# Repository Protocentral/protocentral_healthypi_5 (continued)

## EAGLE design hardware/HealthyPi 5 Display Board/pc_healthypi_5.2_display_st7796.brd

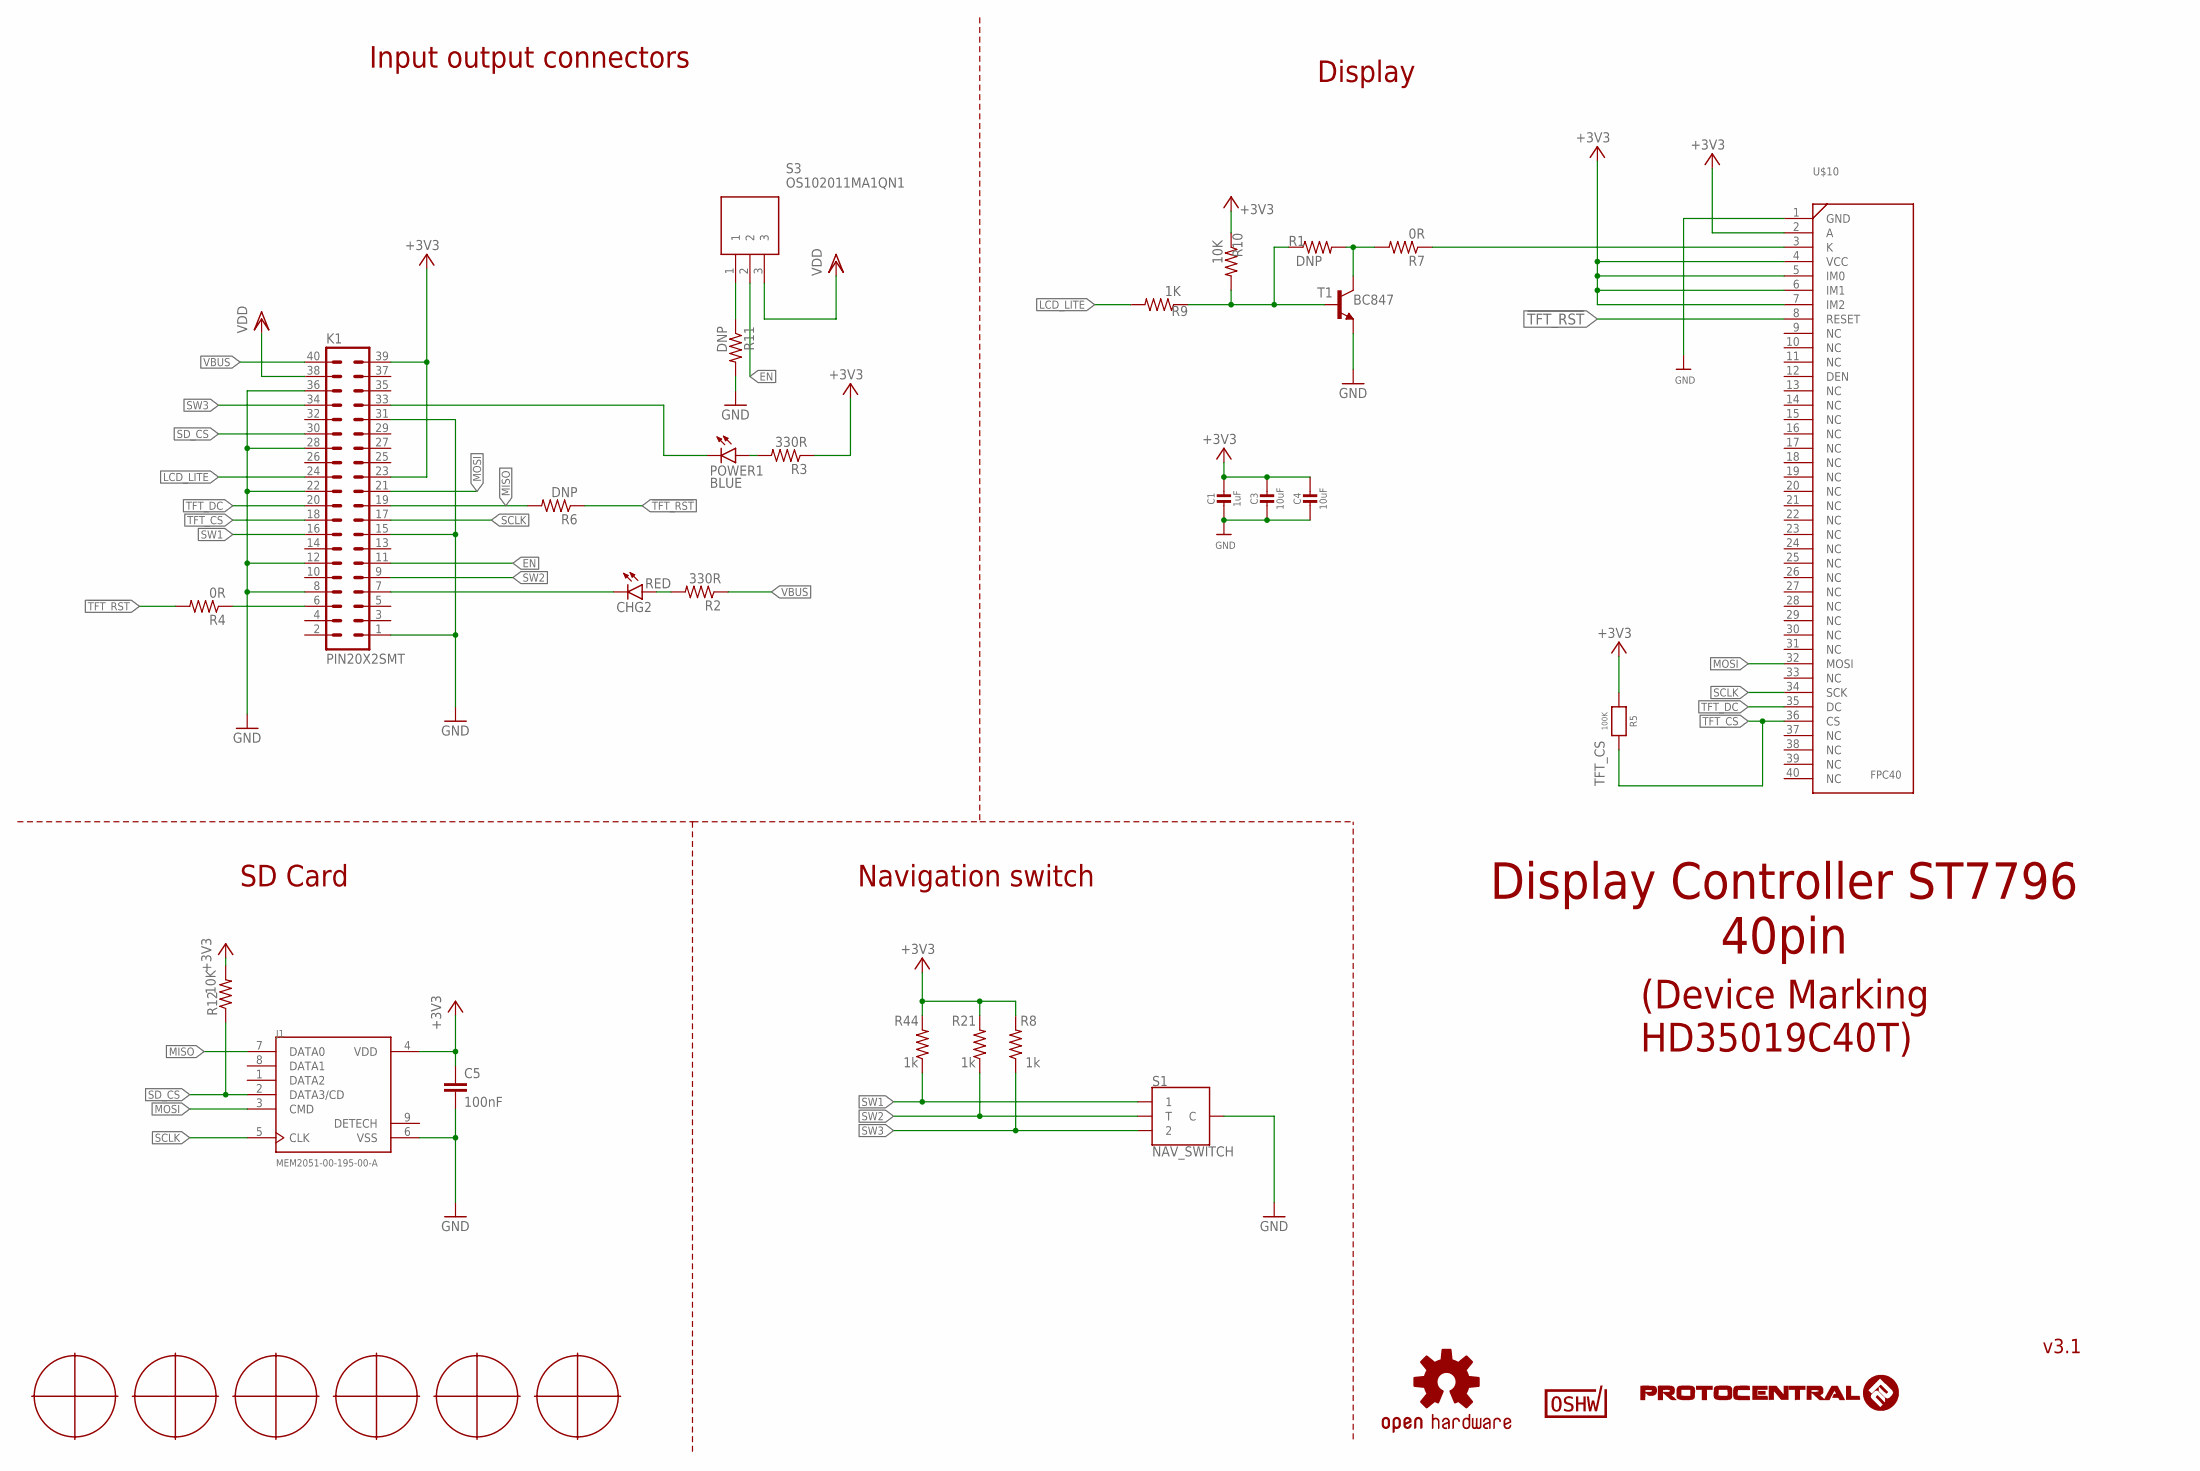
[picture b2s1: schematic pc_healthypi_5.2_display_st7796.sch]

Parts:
C1: 1uF; 0805-NO
C3, C4: 10uF; 0805-NO
C5: 100nF; C0402
CHG2: RED; CHIPLED_0603
J1: MEM2051-00-195-00-A; GCT_MEM2051-00-195-00-A
K1: PIN20X2SMT; 20X2SMT
POWER1: BLUE; CHIPLED_0603
R1, R6, R11: DNP; R0402
R2, R3: 330R; R0402
R4: 0R; R0402
R5: 100K; 0805-NO
R7: 0R; R0805
R8, R21, R44: 1k; 0402
R9: 1K; R0402
R10, R12: 10K; R0402
S1: NAV_SWITCH
S3: OS102011MA1QN1
T1: BC847; SOT23-BEC
U$1, U$3, U$7, U$8, U$23, U$25: FUDCIALPOINTS; FIDUCIALPOINTS
U$5: OSHW-LOGOM; OSHW-LOGO-M
U$10: FPC40; FPC40PIN
U$13: CERT-SMALL; CERT-SMALL-SILK

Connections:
!TFT_RST: R4.2, R6.1, U$10.8 (RESET)
+3V3: C1.1, C3.1, C4.1, C5.1, J1.4 (VDD), K1.23, K1.39, R3.1, R5.2, R8.2, R10.1, R12.2, R21.2, R44.2, U$10.2 (A), U$10.4 (VCC), U$10.5 (IM0), U$10.6 (IM1), U$10.7 (IM2)
EN: K1.11, S3.2
GND: C1.2, C3.2, C4.2, C5.2, J1.6 (VSS), K1.1, K1.8, K1.12, K1.15, K1.22, K1.28, K1.31, K1.36, R11.2, S1.C, T1.E, U$10.1 (GND)
LCD_LITE: K1.24, R9.2
LED1: K1.33, POWER1.C
MISO: J1.7 (DATA0), K1.19, R6.2
MOSI: J1.3 (CMD), K1.21, U$10.32 (MOSI)
unnamed: R1.2, R7.2, T1.C
unnamed: CHG2.C, K1.7
unnamed: K1.6, R4.1
unnamed: R7.1, U$10.3 (K)
unnamed: POWER1.A, R3.2
unnamed: CHG2.A, R2.2
unnamed: R11.1, S3.1
unnamed: R1.1, R9.1, R10.2, T1.B
SCLK: J1.5 (CLK), K1.17, U$10.34 (SCK)
SD_CS: J1.2 (DATA3/CD), K1.30, R12.1
SW1: K1.16, R44.1, S1.1
SW2: K1.9, R21.1, S1.T
SW3: K1.34, R8.1, S1.2
TFT_CS: K1.18, R5.1, U$10.36 (CS)
TFT_DC: K1.20, U$10.35 (DC)
VBUS: K1.40, R2.1
VDD: K1.38, S3.3

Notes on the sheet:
Display Controller ST7796 40pin
(Device Marking HD35019C40T)
Input output connectors
Display
SD Card
Navigation switch
v3.1

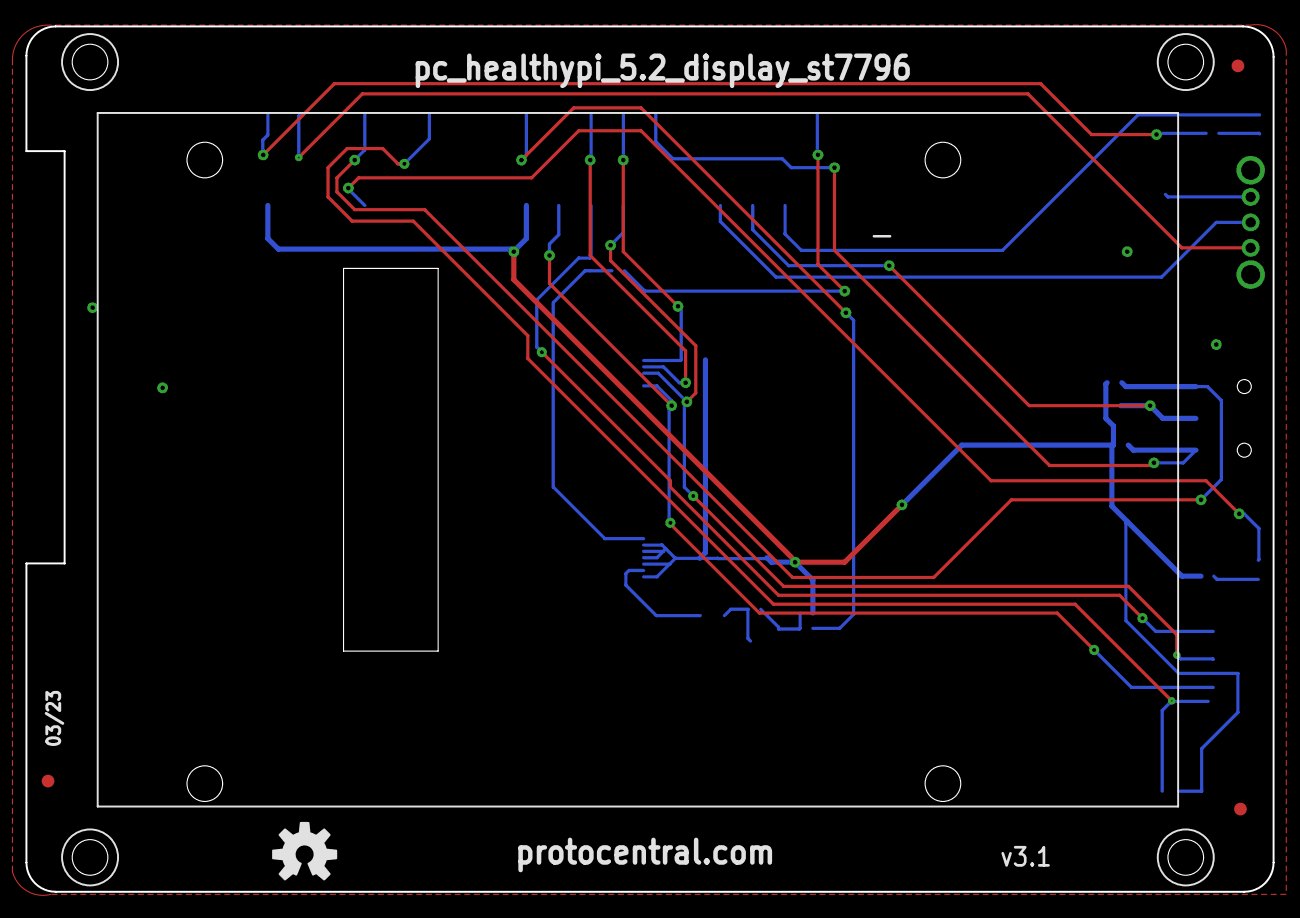
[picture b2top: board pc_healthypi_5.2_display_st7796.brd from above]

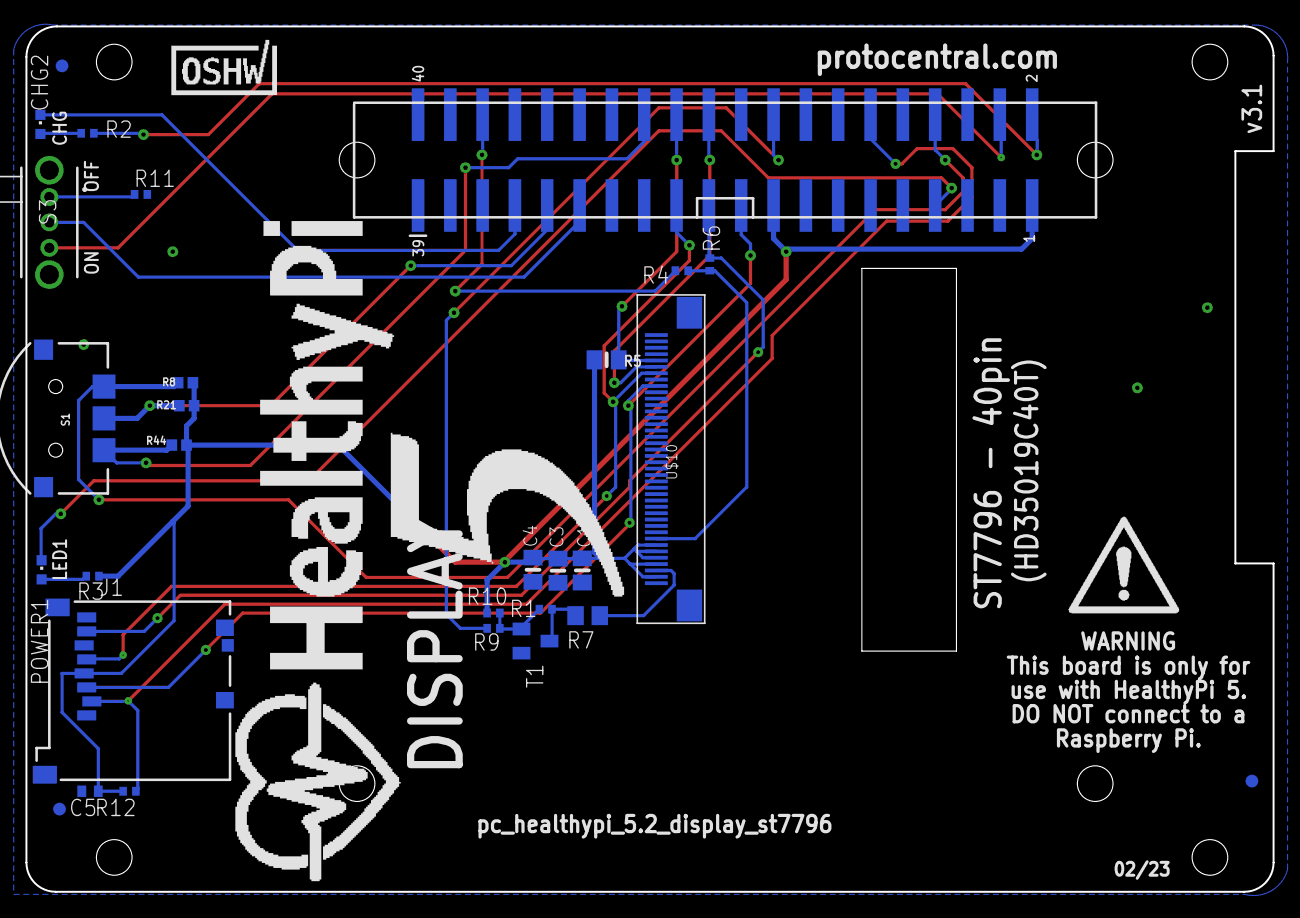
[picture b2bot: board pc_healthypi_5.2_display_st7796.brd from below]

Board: 2 copper layers, 98.0 x 68.0 mm, 36 parts (32 on the bottom side), 25 nets.

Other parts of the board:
U$9: WARNINGSYM
U$20: HEALTHYPIV5LOGO

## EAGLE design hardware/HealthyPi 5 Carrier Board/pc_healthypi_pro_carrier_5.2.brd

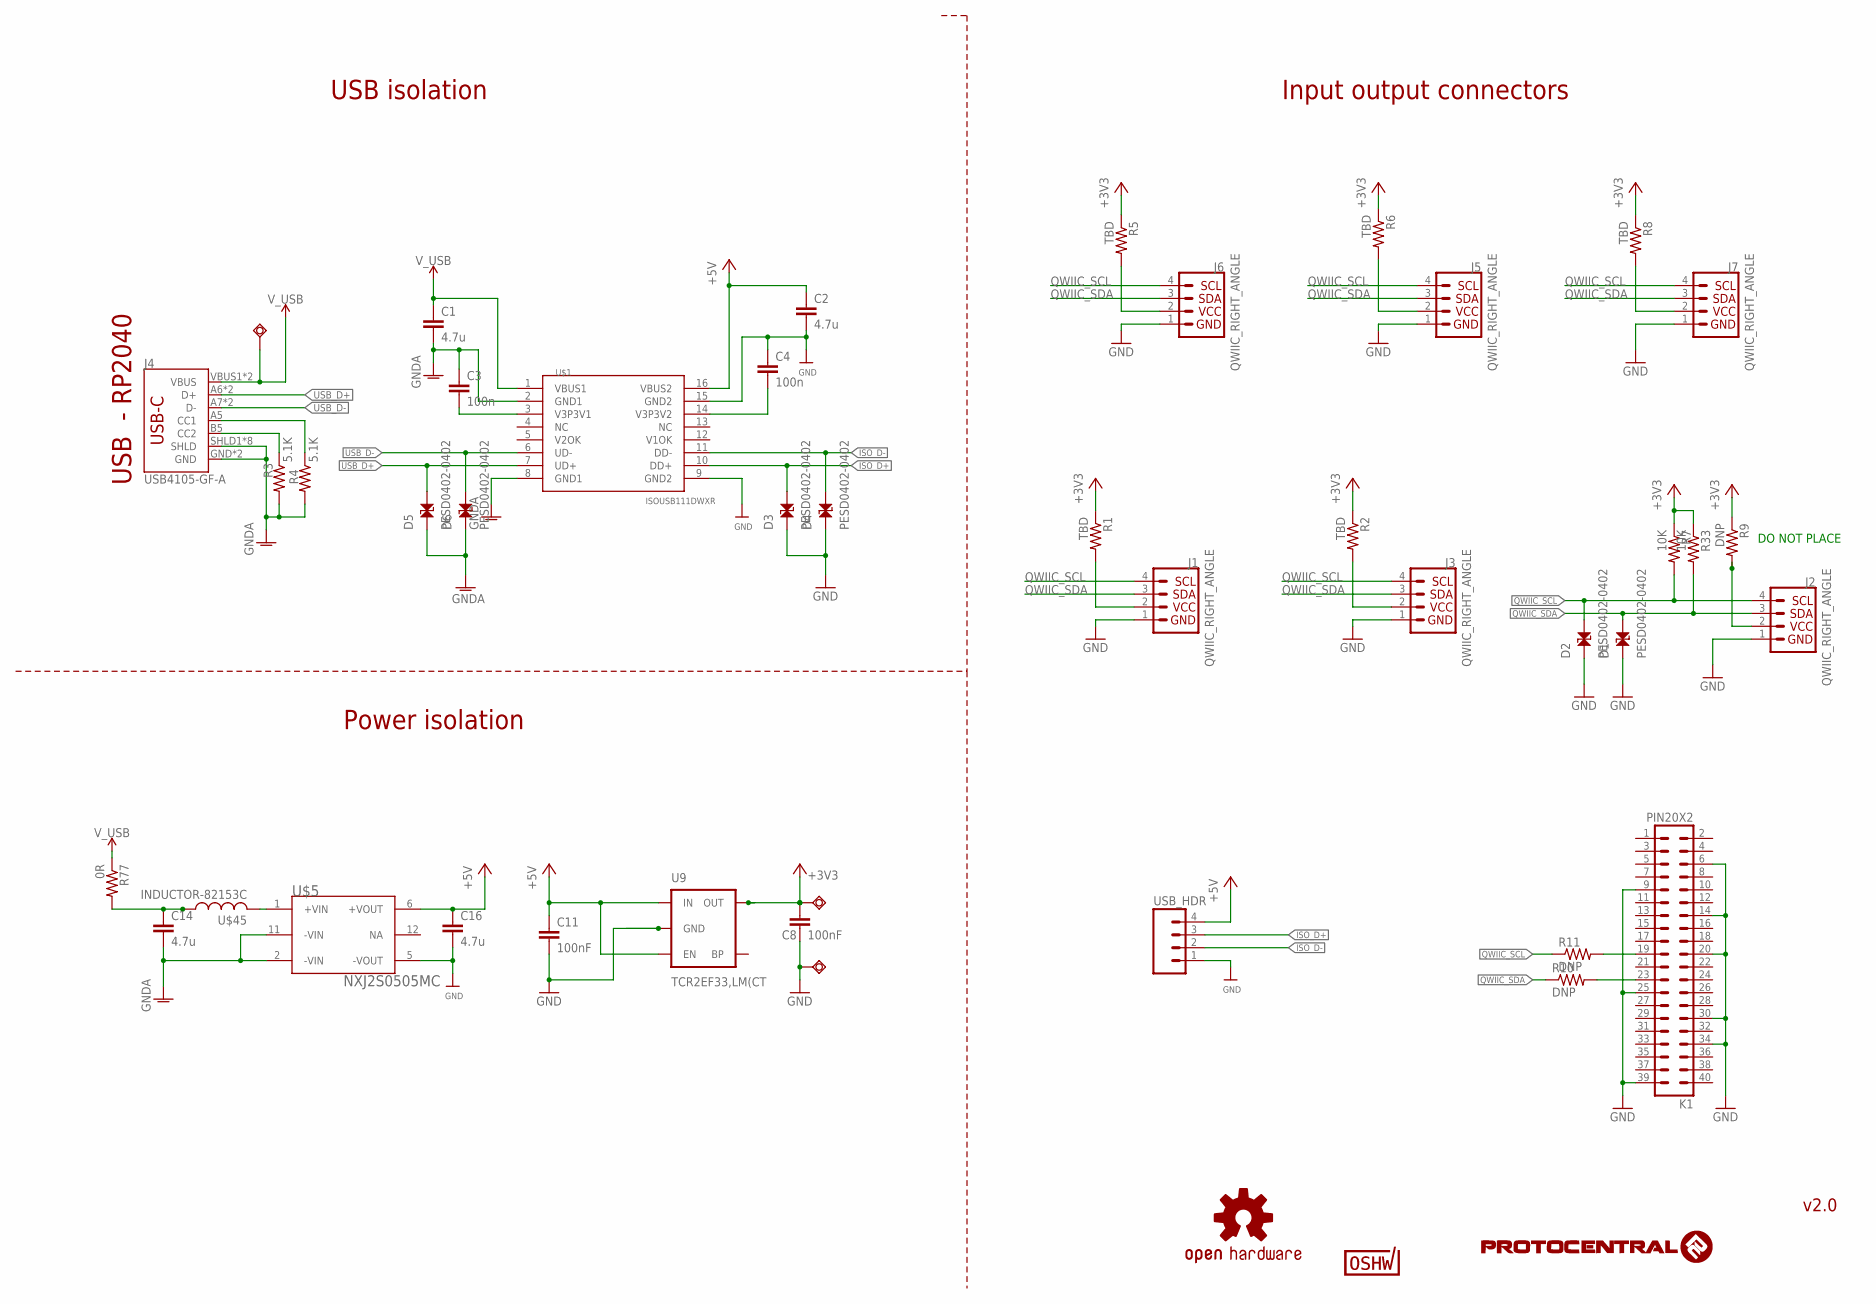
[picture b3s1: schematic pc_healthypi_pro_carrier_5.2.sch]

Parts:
C1, C2, C14, C16: 4.7u; C0805
C3, C4: 100n; C0402
C8, C11: 100nF; C0402
D1, D2, D3, D4, D5, D6: PESD0402-0402; 0402
J1, J2, J3, J5, J6, J7: QWIIC_RIGHT_ANGLE; JST04_1MM_RA
J4: USB4105-GF-A; USB-C-16P
K1: PIN20X2; PIN_20X2
R1, R2, R5, R6, R8: TBD; R0402
R3, R4: 5.1K; R0402
R7, R33: 10K; R0402
R9, R10, R11: DNP; R0402
R77: 0R; R0805
SWIO5, SWIO6: TPSQTP11R; TP11R
TP8: TPSQTP11R; TP11R
U9: TCR2EF33,LM(CT; SOT23-5
U$1: ISOUSB111DWXR; SSOP-16-5.85X7.5
U$5: NXJ2S0505MC
U$13: CERT-SMALL; CERT-SMALL-SILK
U$42: OSHW-LOGOM; OSHW-LOGO-M
U$45: INDUCTOR-82153C; INDUCTOR-8200
USB_HDR: M04LOCK_LONGPADS; 1X04_LOCK_LONGPADS

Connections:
+3V3: C8.1, R1.1, R2.1, R5.1, R6.1, R7.1, R8.1, R9.1, R33.1, SWIO5.TP, U9.5 (OUT)
+5V: C2.1, C11.1, C16.1, U9.1 (IN), U9.3 (EN), U$1.16 (VBUS2), U$5.6 (+VOUT), USB_HDR.4
GND: C2.2, C4.1, C8.2, C11.2, C16.2, D1.1, D2.1, D3.1, D4.1, J1.1, J2.1, J3.1, J5.1, J6.1, J7.1, K1.6, K1.9, K1.14, K1.20, K1.25, K1.30, K1.34, K1.39, SWIO6.TP, U9.2 (GND), U$1.9 (GND2), U$1.15 (GND2), U$5.5 (-VOUT), USB_HDR.1
GNDA: C1.2, C3.1, C14.2, D5.1, D6.1, J4.GND, J4.GND2 (GND), J4.SHLD1 (SHLD), J4.SHLD2 (SHLD), J4.SHLD3 (SHLD), J4.SHLD4 (SHLD), J4.SHLD5 (SHLD), J4.SHLD6 (SHLD), J4.SHLD7 (SHLD), J4.SHLD8 (SHLD), R3.2, R4.2, U$1.2 (GND1), U$1.8 (GND1), U$5.2 (-VIN), U$5.11 (-VIN)
ISO_D+: D3.2, U$1.10 (DD+), USB_HDR.3
ISO_D-: D4.2, U$1.11 (DD-), USB_HDR.2
unnamed: J1.2, R1.2
unnamed: J3.2, R2.2
unnamed: J6.2, R5.2
unnamed: J5.2, R6.2
unnamed: J7.2, R8.2
unnamed: J2.2, R9.2
unnamed: C3.2, U$1.3 (V3P3V1)
unnamed: C4.2, U$1.14 (V3P3V2)
unnamed: K1.23, R10.2
unnamed: K1.19, R11.2
unnamed: J4.B5 (CC2), R3.1
unnamed: J4.A5 (CC1), R4.1
unnamed: U$5.1 (+VIN), U$45.P$2 (2)
unnamed: C14.1, R77.2, U$45.P$1 (1)
QWIIC_SCL: D2.2, J1.4, J2.4, J3.4, J5.4, J6.4, J7.4, R7.2, R11.1
QWIIC_SDA: D1.2, J1.3, J2.3, J3.3, J5.3, J6.3, J7.3, R10.1, R33.2
USB_D+: D5.2, J4.A6 (D+), J4.B6 (D+), U$1.7 (UD+)
USB_D-: D6.2, J4.A7 (D-), J4.B7 (D-), U$1.6 (UD-)
V_USB: C1.1, J4.VBUS1 (VBUS), J4.VBUS2 (VBUS), R77.1, TP8.TP, U$1.1 (VBUS1)

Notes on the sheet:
USB - RP2040
DO NOT PLACE
USB isolation
Input output connectors
Power isolation
v2.0

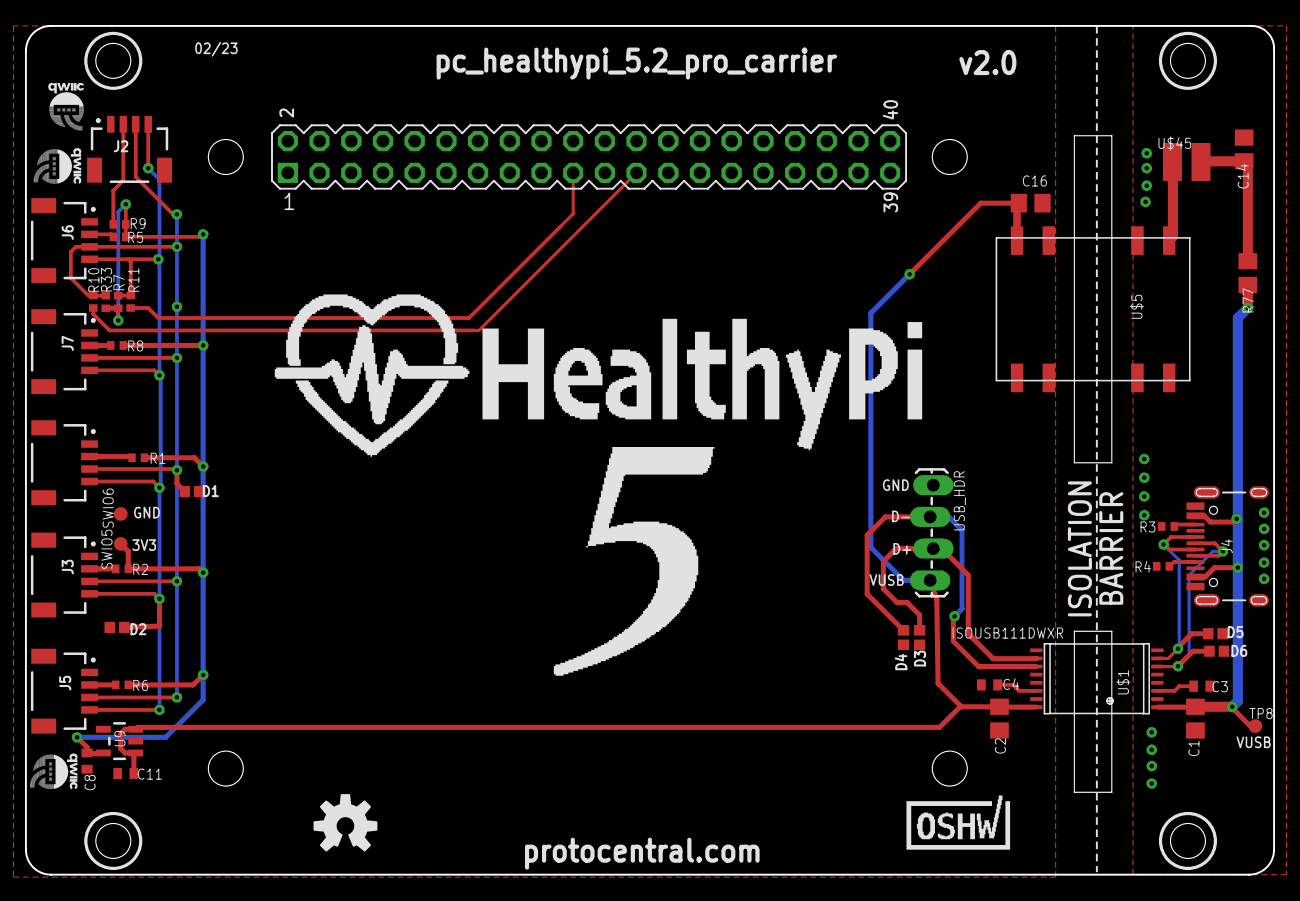
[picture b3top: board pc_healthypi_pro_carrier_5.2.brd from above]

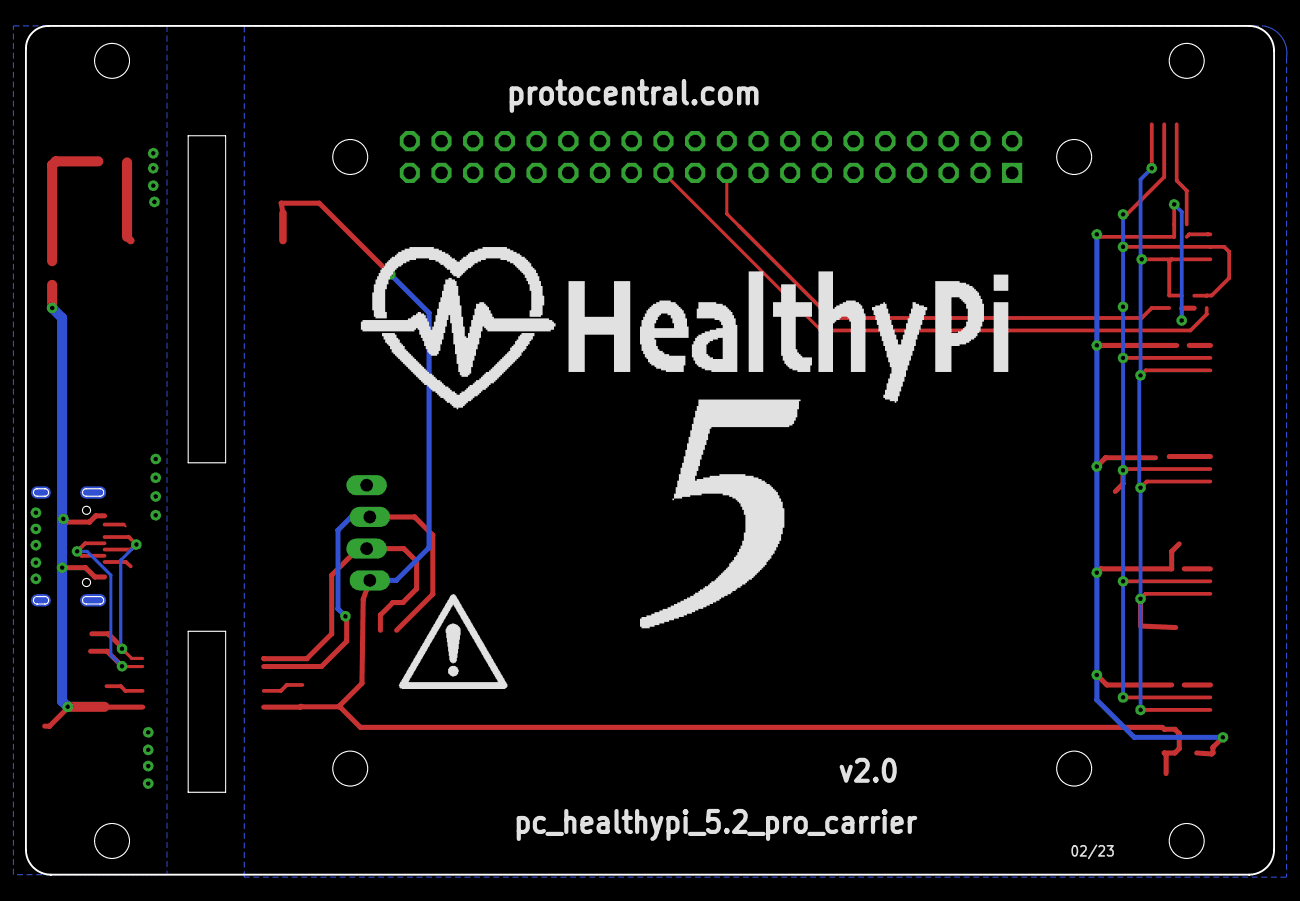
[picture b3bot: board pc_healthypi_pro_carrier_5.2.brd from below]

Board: 2 copper layers, 100.0 x 68.0 mm, 51 parts (2 on the bottom side), 25 nets.

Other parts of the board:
U$6, U$15, U$59: QWIIC#LABEL#FULL#M#PNG
U$7, U$20: HEALTHYPIV5LOGO
U$17: WARNINGSYM

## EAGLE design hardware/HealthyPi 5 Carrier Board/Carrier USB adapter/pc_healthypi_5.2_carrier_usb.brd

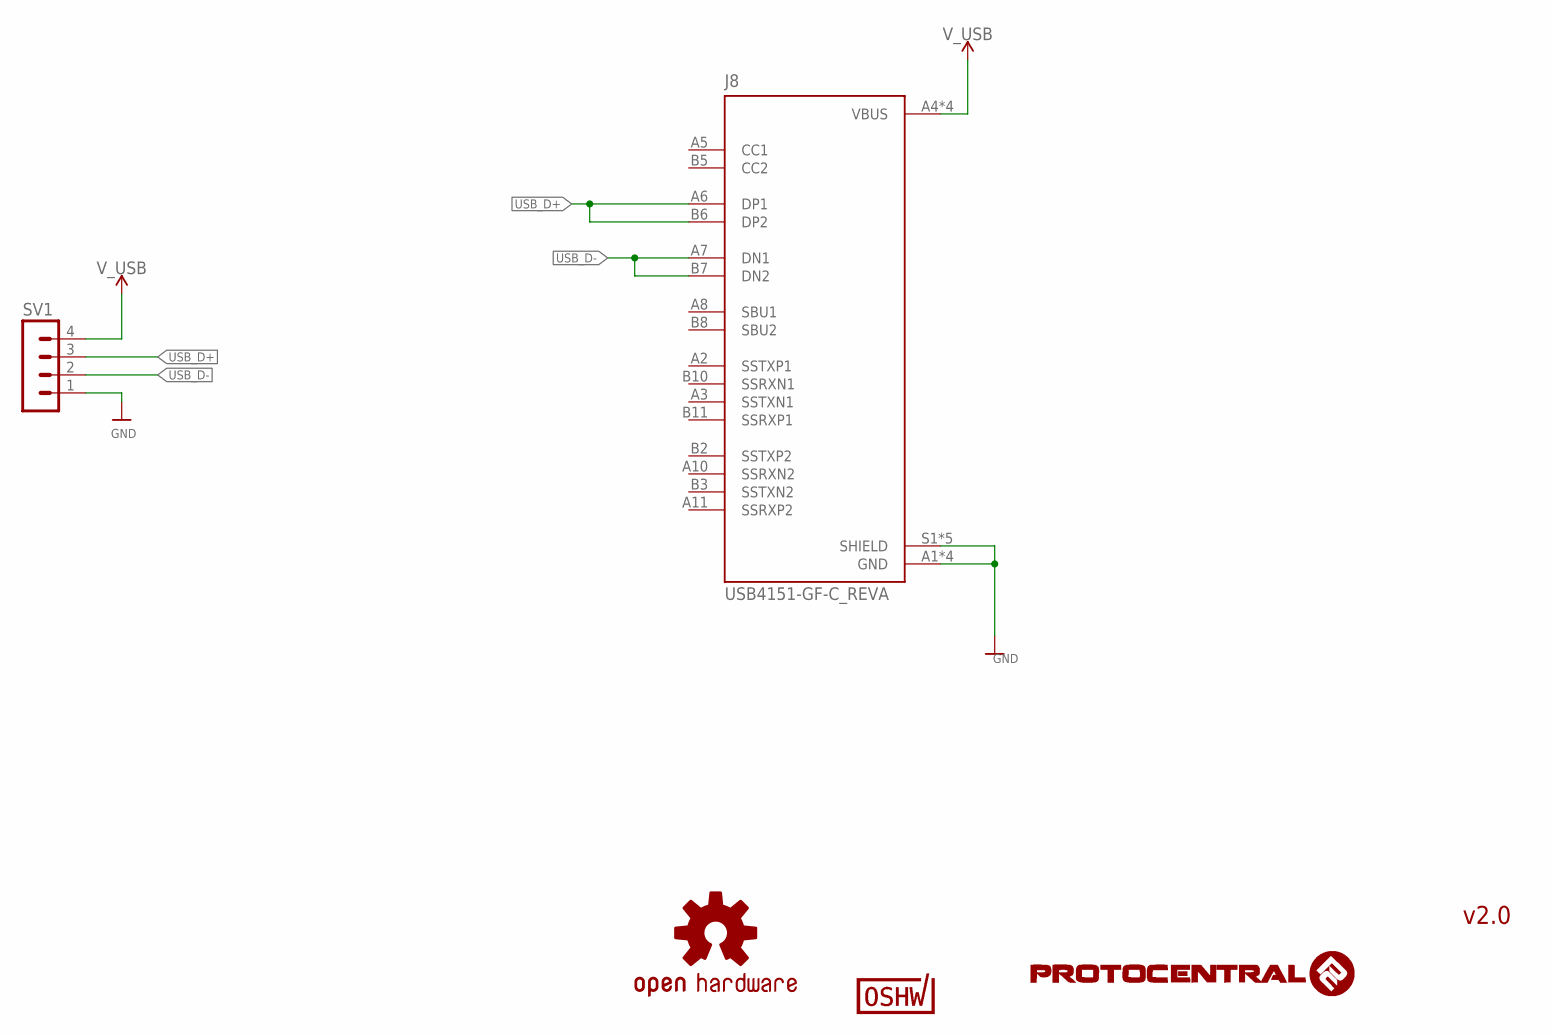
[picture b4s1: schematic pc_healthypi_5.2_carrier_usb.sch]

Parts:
J8: USB4151-GF-C_REVA; GCT_USB4151-GF-C_REVA
SV1: MA04-1
U$13: CERT-SMALL; CERT-SMALL-SILK
U$42: OSHW-LOGOM; OSHW-LOGO-M

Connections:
GND: J8.A1 (GND), J8.A12 (GND), J8.B1 (GND), J8.B12 (GND), J8.S1 (SHIELD), J8.S2 (SHIELD), J8.S3 (SHIELD), J8.S4 (SHIELD), J8.S5 (SHIELD), SV1.1
USB_D+: J8.A6 (DP1), J8.B6 (DP2), SV1.3
USB_D-: J8.A7 (DN1), J8.B7 (DN2), SV1.2
V_USB: J8.A4 (VBUS), J8.A9 (VBUS), J8.B4 (VBUS), J8.B9 (VBUS), SV1.4

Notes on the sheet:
v2.0

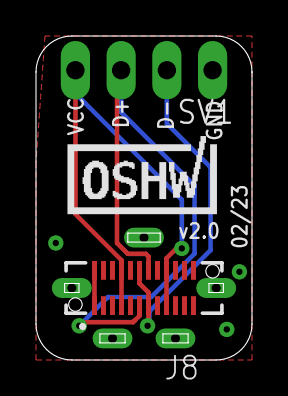
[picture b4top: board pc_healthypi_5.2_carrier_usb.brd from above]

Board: 4 copper layers, 12.0 x 18.0 mm, 4 parts (1 on the bottom side), 4 nets.

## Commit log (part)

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2023-04-26 Initial public commit
2023-05-17 Plot with fixed scale in mV
2023-07-17 Add docs
2023-07-18 Added Sphinx docs
2023-07-18 Add hardware doc
2023-08-15 Disabled LSL support
2023-08-15 Remove GUI limits in plot
2023-08-16 Added SpO2 HR, RR fields from device
2024-12-02 Added schematics upto HealthyPi 5.7
